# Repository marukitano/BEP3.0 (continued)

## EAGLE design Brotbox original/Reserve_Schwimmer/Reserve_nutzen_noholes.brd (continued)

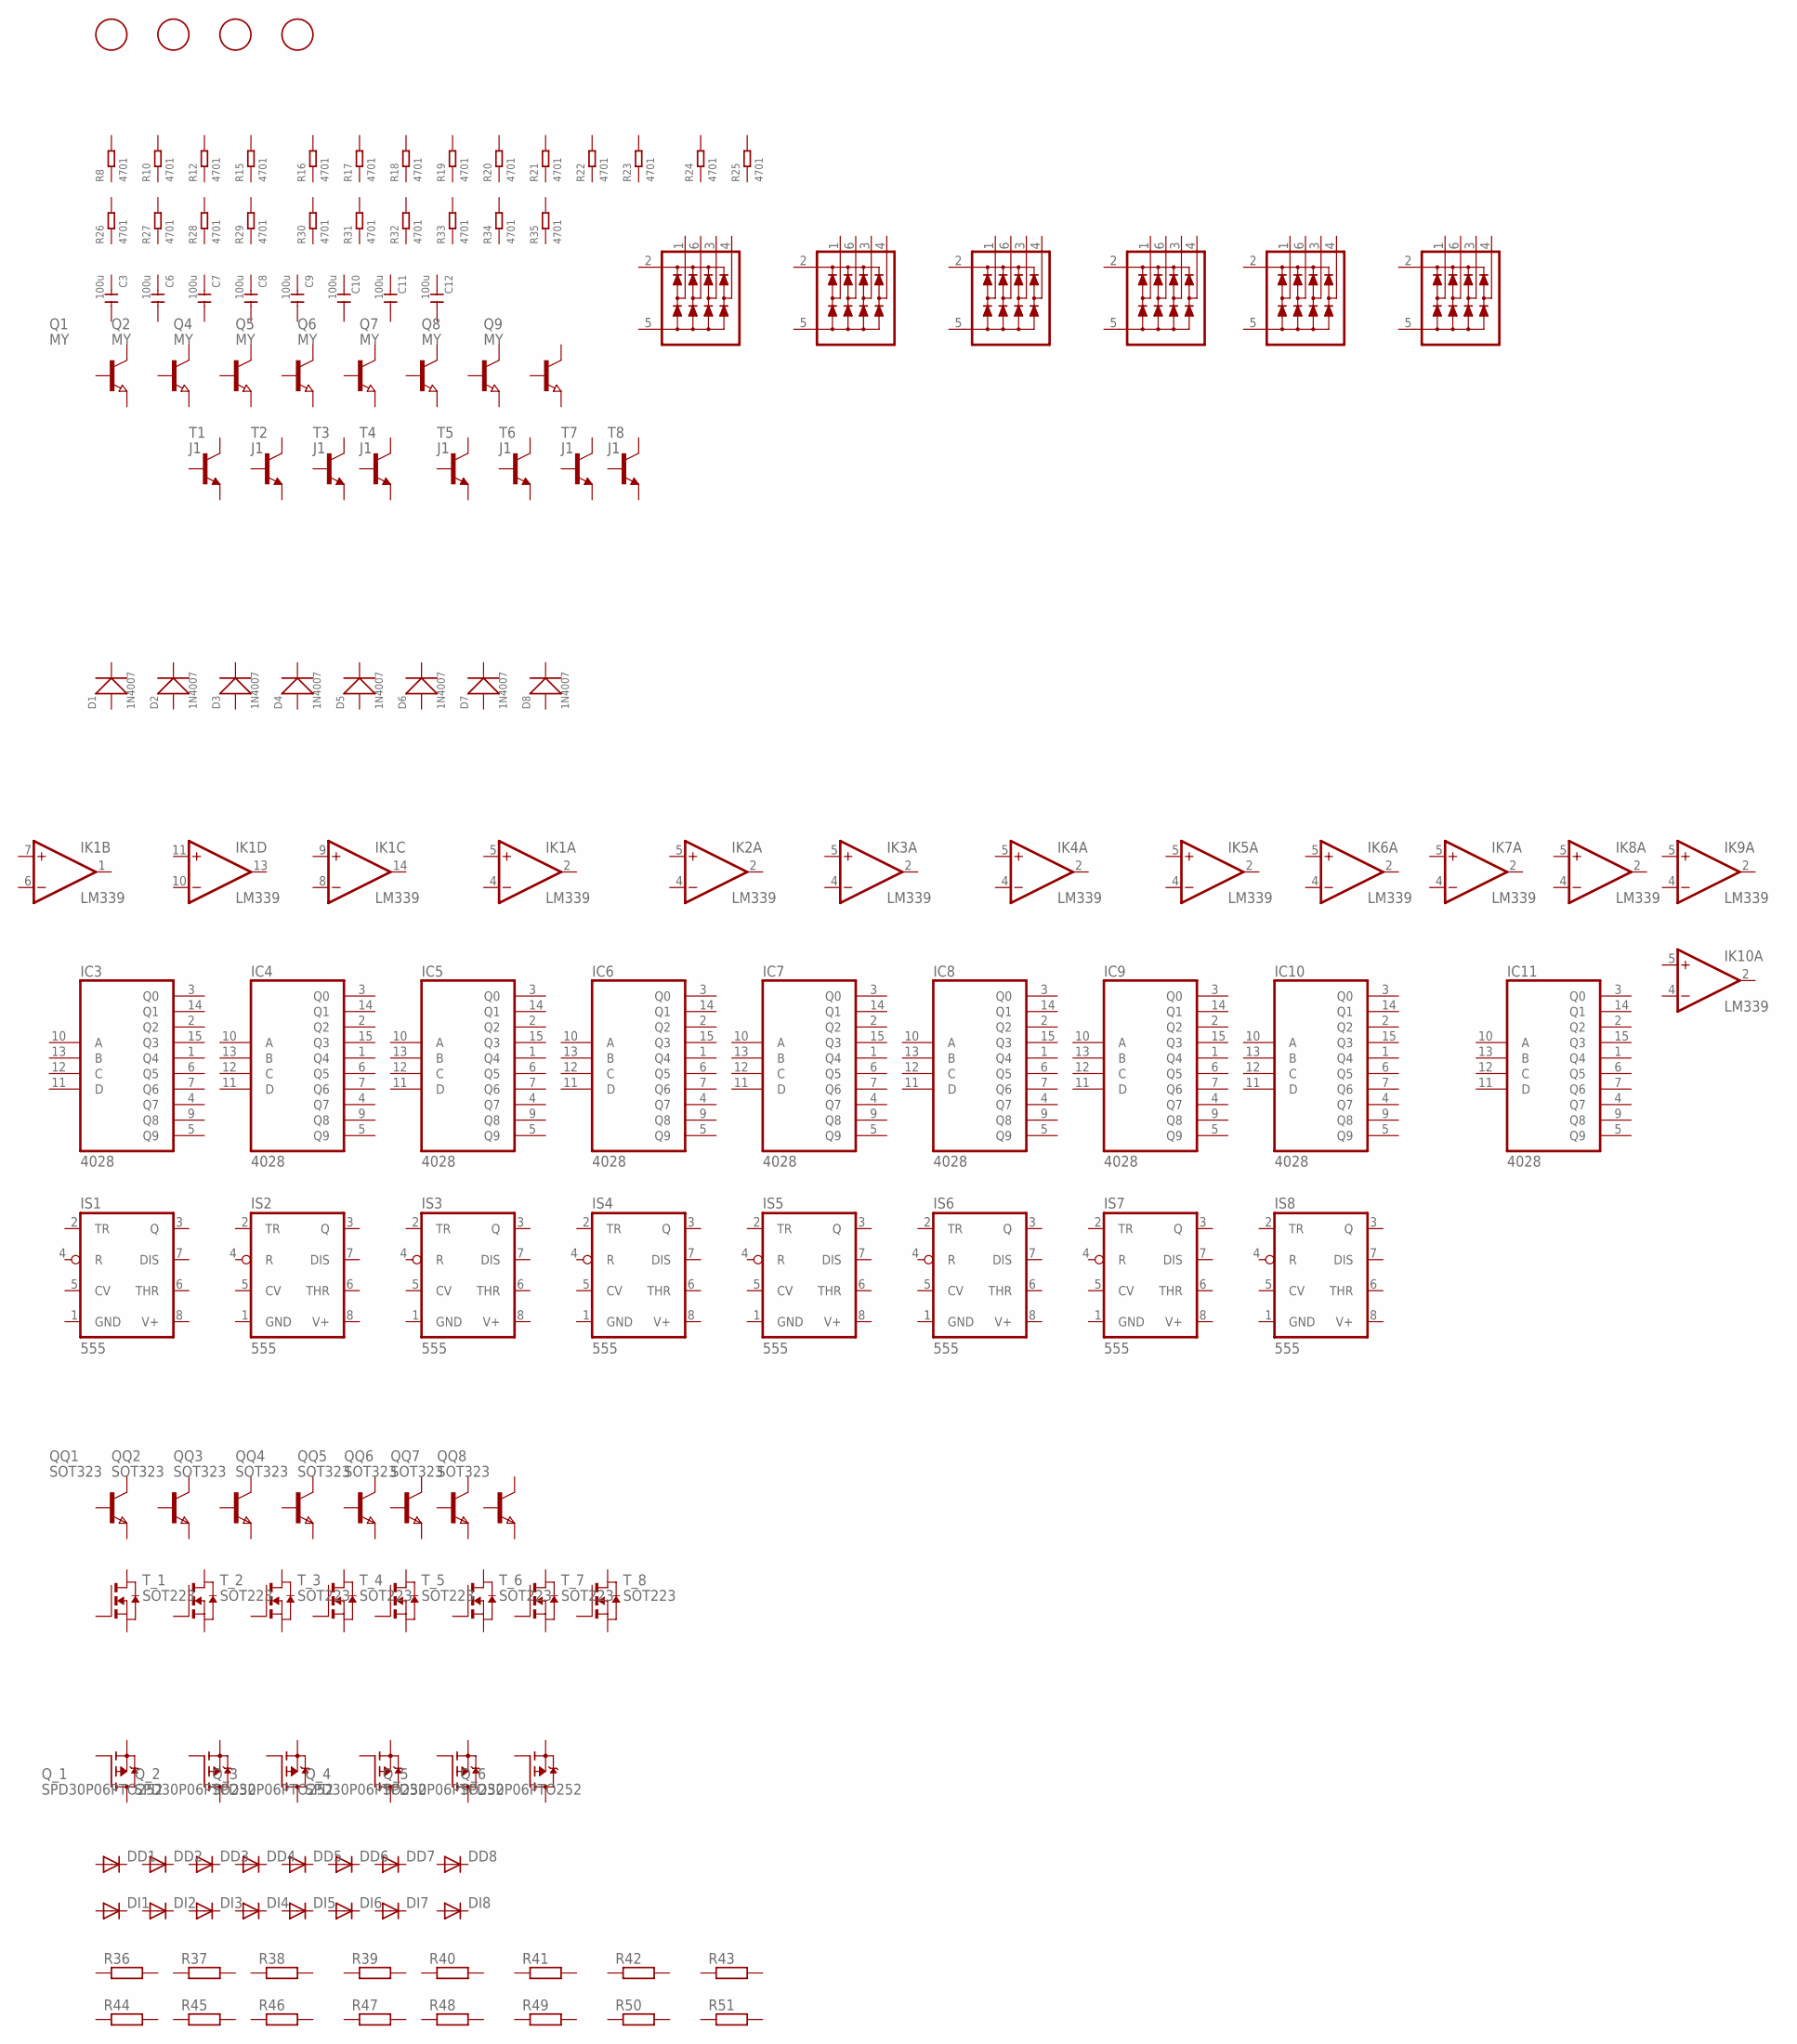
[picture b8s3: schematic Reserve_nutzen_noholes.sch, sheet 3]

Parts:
C3, C6, C7, C8, C9, C10, C11, C12: 100u; C1206
D1, D2, D3, D4, D5, D6, D7, D8: 1N4007; DO-214AC
DD1, DD2, DD3, DD4, DD5, DD6, DD7, DD8: DIODE-SOD123; SOD123
DI1, DI2, DI3, DI4, DI5, DI6, DI7, DI8: DIODE-SOD323-R; SOD323-R
FID1_: FID2; FIDUCIAL_1MM
FID2: FID1; FIDUCIAL_1MM
FID3_, FID4: FIDUCIAL; FIDUCIAL_1MM
IC3, IC4, IC5, IC6, IC7, IC8, IC9, IC10, IC11: 4028; SO16
IK1, IK2, IK3, IK4, IK5, IK6, IK7, IK8, IK9, IK10: LM339; SO14
IS1, IS2, IS3, IS4, IS5, IS6, IS7, IS8: 555; SO08
Q1, Q2, Q4, Q5, Q6, Q7, Q8, Q9: MY; SOT89
QQ1, QQ2, QQ3, QQ4, QQ5, QQ6, QQ7, QQ8: SOT323
Q_1, Q_2, Q_3, Q_4, Q_5, Q_6: SPD30P06PTO252; TO252
R8, R10, R12, R15, R16, R17, R18, R19, R20, R21, R22, R23, R24, R25, R26, R27, R28, R29, R30, R31, R32, R33, R34, R35: 4701; R0805
R36, R37, R38, R39, R40, R41, R42, R43: R-EU_R0603; R0603
R44, R45, R46, R47, R48, R49, R50, R51: R-EU_R0402; R0402
T1, T2, T3, T4, T5, T6, T7, T8: J1; SOT23-BEC
T_1, T_2, T_3, T_4, T_5, T_6, T_7, T_8: SOT223
U1, U2, U3, U4, U5, U6: NUP4304SOT457_R; SOT457R_PHILIPS

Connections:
GND1: IK1.12 (GND), IK2.12 (GND), IK3.12 (GND), IK4.12 (GND), IK5.12 (GND), IK6.12 (GND), IK7.12 (GND), IK8.12 (GND), IK9.12 (GND), IK10.12 (GND), IS1.1 (GND), IS2.1 (GND), IS3.1 (GND), IS4.1 (GND), IS5.1 (GND), IS6.1 (GND), IS7.1 (GND), IS8.1 (GND)
V+: IK1.3 (V+), IK2.3 (V+), IK3.3 (V+), IK4.3 (V+), IK5.3 (V+), IK6.3 (V+), IK7.3 (V+), IK8.3 (V+), IK9.3 (V+), IK10.3 (V+), IS1.8 (V+), IS2.8 (V+), IS3.8 (V+), IS4.8 (V+), IS5.8 (V+), IS6.8 (V+), IS7.8 (V+), IS8.8 (V+)
VDD: IC3.16 (VDD), IC4.16 (VDD), IC5.16 (VDD), IC6.16 (VDD), IC7.16 (VDD), IC8.16 (VDD), IC9.16 (VDD), IC10.16 (VDD), IC11.16 (VDD)
VSS: IC3.8 (VSS), IC4.8 (VSS), IC5.8 (VSS), IC6.8 (VSS), IC7.8 (VSS), IC8.8 (VSS), IC9.8 (VSS), IC10.8 (VSS), IC11.8 (VSS)

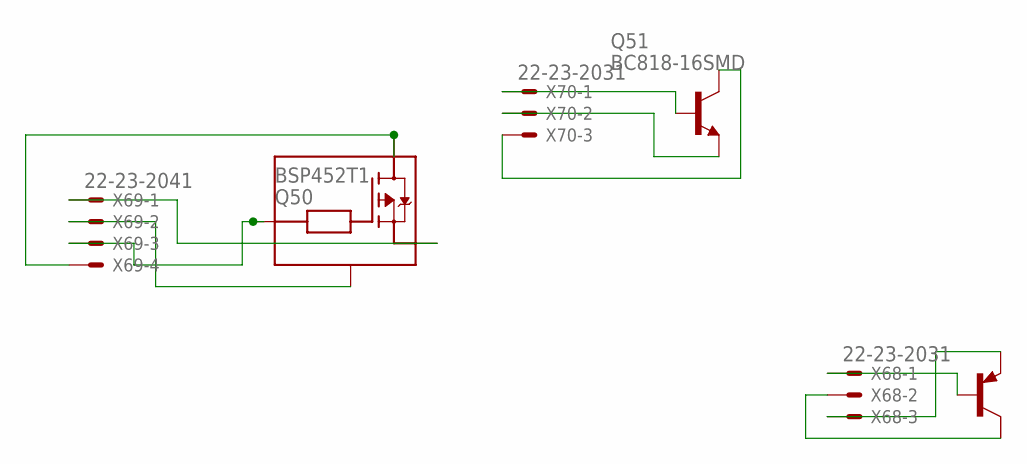
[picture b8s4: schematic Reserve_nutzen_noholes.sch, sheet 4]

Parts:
Q49: BCP53T1; SOT223
Q50: BSP452T1; SOT223
Q51: BC818-16SMD; SOT23-BEC
X68, X70: 22-23-2031
X69: 22-23-2041

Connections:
unnamed: Q49.1 (B), X68.1
unnamed: Q49.2 (C), X68.2
unnamed: Q49.3 (E), X68.3
unnamed: Q50.1 (OUT), X69.1
unnamed: Q50.2 (GND), X69.2
unnamed: Q50.3 (IN), X69.3
unnamed: Q50.4 (V+), X69.4
unnamed: Q51.B, X70.1
unnamed: Q51.E, X70.2
unnamed: Q51.C, X70.3

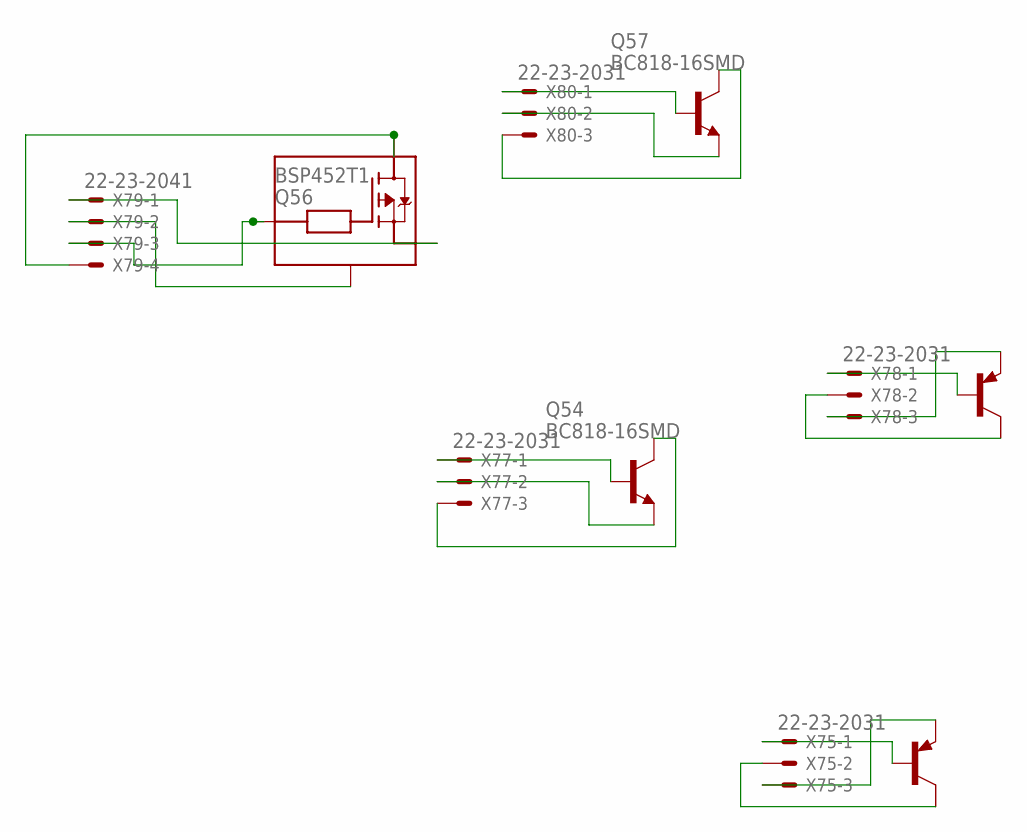
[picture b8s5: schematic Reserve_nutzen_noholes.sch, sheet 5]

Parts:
Q52, Q55: BCP53T1; SOT223
Q54, Q57: BC818-16SMD; SOT23-BEC
Q56: BSP452T1; SOT223
X75, X77, X78, X80: 22-23-2031
X79: 22-23-2041

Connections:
unnamed: Q52.1 (B), X75.1
unnamed: Q52.2 (C), X75.2
unnamed: Q52.3 (E), X75.3
unnamed: Q54.B, X77.1
unnamed: Q54.E, X77.2
unnamed: Q54.C, X77.3
unnamed: Q55.1 (B), X78.1
unnamed: Q55.2 (C), X78.2
unnamed: Q55.3 (E), X78.3
unnamed: Q56.1 (OUT), X79.1
unnamed: Q56.2 (GND), X79.2
unnamed: Q56.3 (IN), X79.3
unnamed: Q56.4 (V+), X79.4
unnamed: Q57.B, X80.1
unnamed: Q57.E, X80.2
unnamed: Q57.C, X80.3

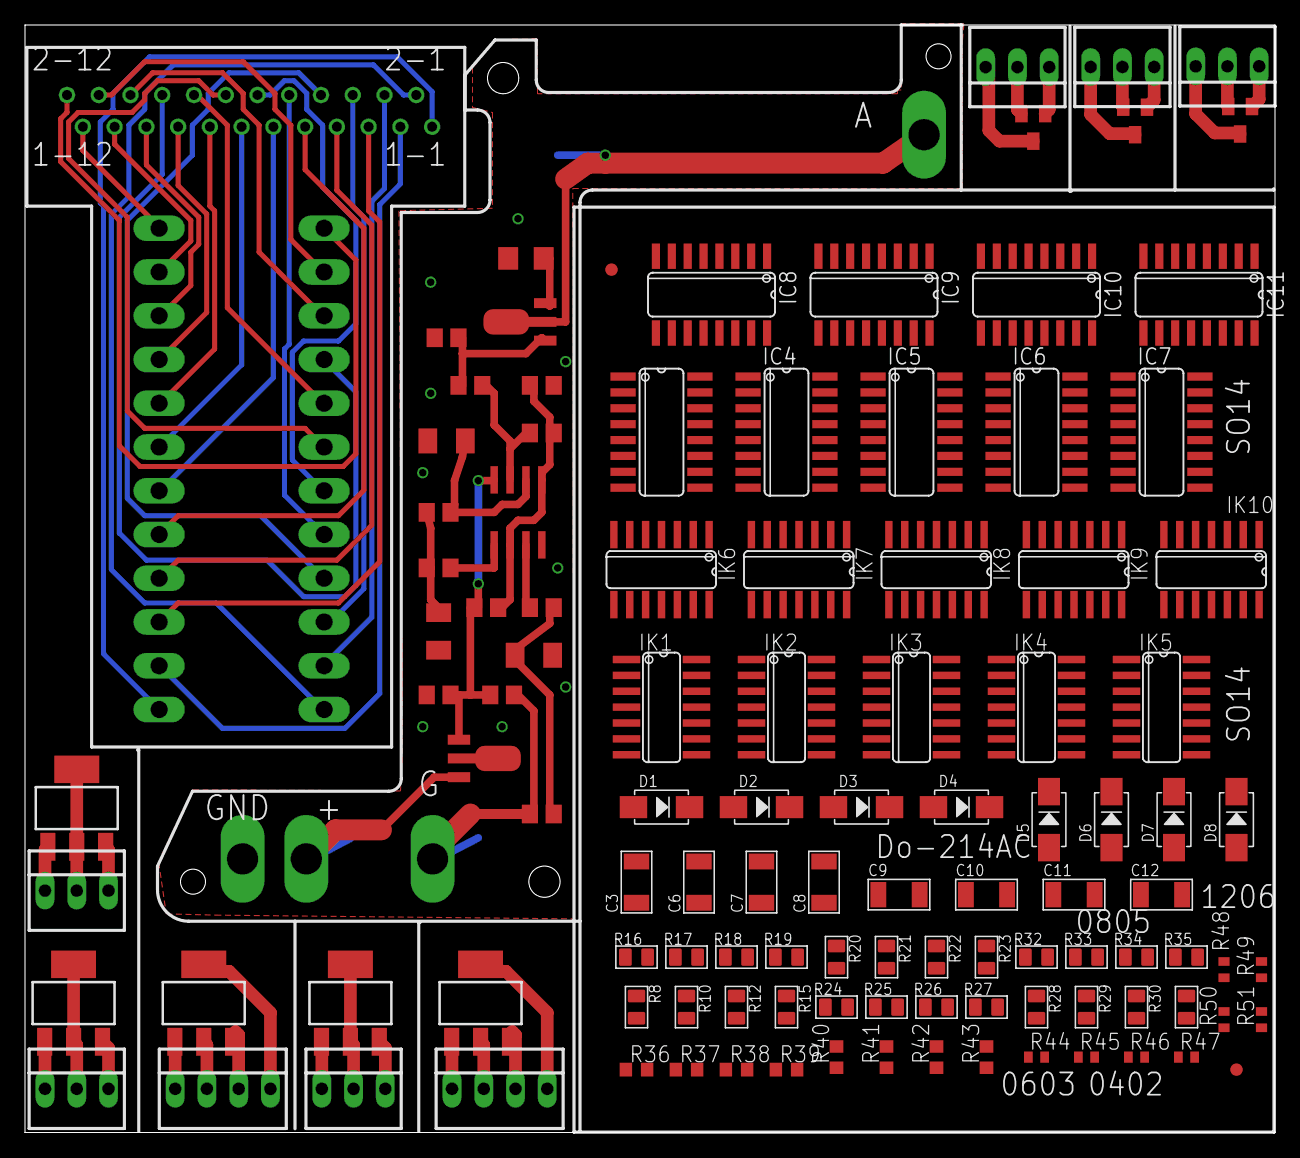
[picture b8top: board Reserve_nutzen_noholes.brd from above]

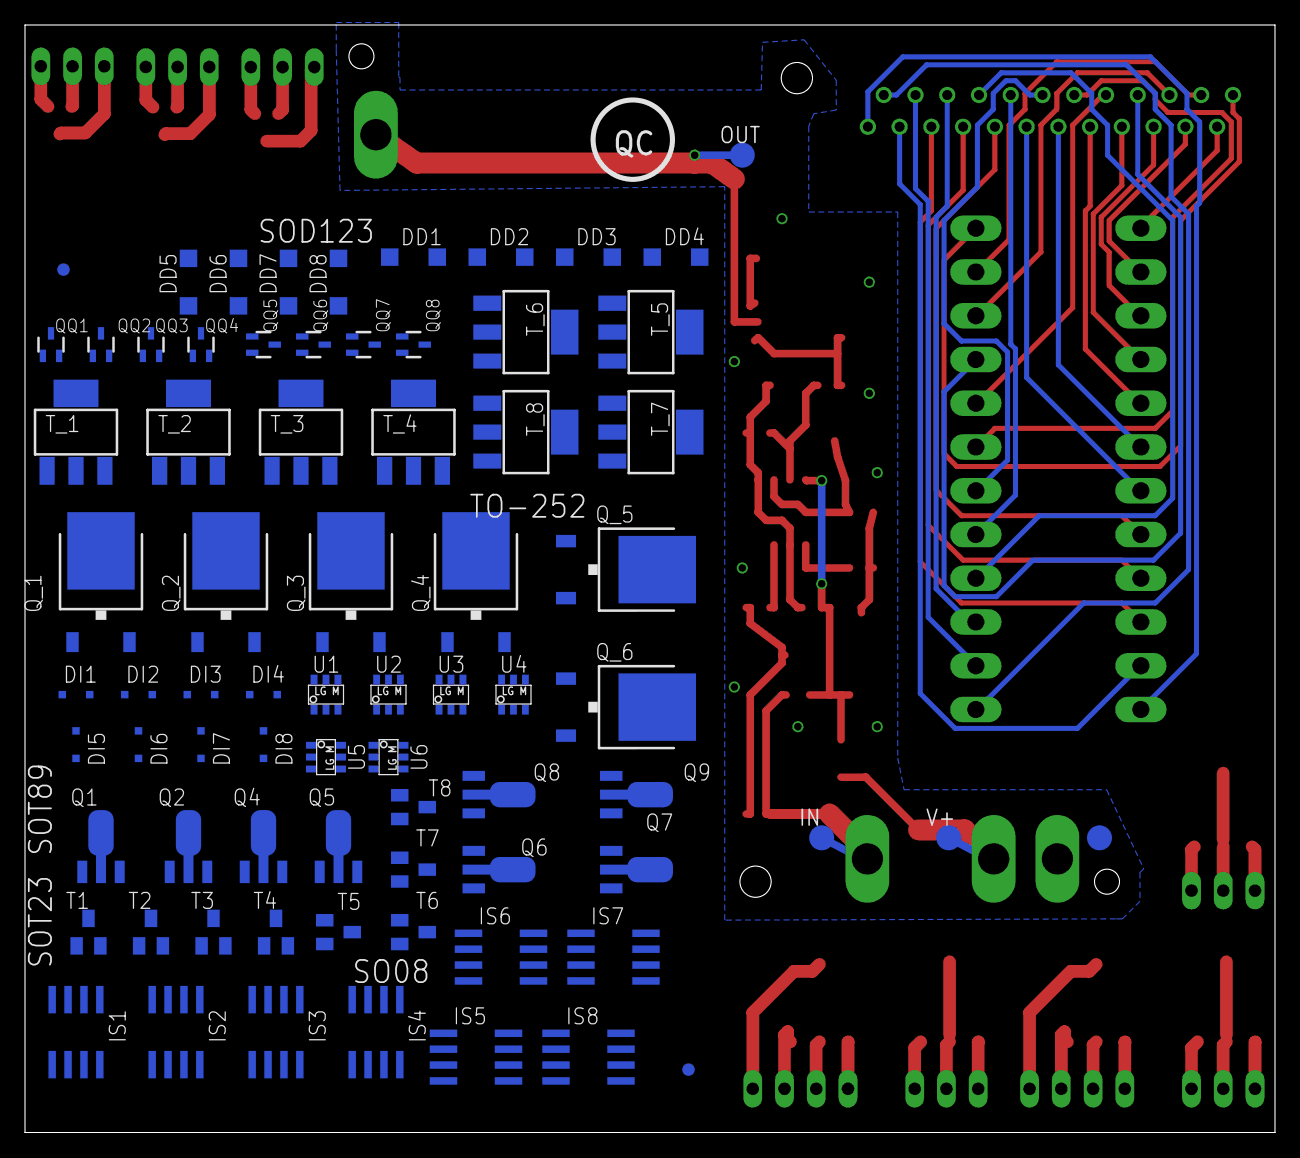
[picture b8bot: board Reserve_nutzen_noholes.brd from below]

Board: 2 copper layers, 100.0 x 88.6 mm, 191 parts (74 on the bottom side), 68 nets.
